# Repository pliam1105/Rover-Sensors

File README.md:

# Rover Sensors

## Overview
A prototype of a rover that can be used to collect data, in order to determine the habitability of a planet.

## Sensors
This rover contains the following sensors:
* Temperature-Humidity
* Gas
* Light
* Pressure and Altitude
* Air Quality
* UV
* GPS
* Geiger Radiation Counter

As well as an ESP-8266 Wi-Fi module for data transmission.<br>
These sensors and the Wi-Fi module are connected to an Arduino Mega (an Arduino Uno is also used between the Geiger Counter and the Arduino Mega). The Arduino in turn transmits the data, via some PHP files, to a database.

The sensors are connected to the Arduino using a custom-designed PCB, made using Fritzing:

<div style="overflow: hidden; width: 100%;">

</div>

## Database
The data of the sensors are stored on a MySQL database, currently on a shared hosting service.

The communication with the database is achieved via some [PHP files](RoverSensorsWeb/data_json.php), hosted on the website, which have access to database. 

## Website ([Link](http://pliamprojects.000webhostapp.com/rover))

The data can be accesed using the website, in the following way:

First, the user selects the mission, given a list of all available missions and their information.<br>
Then, on the home page, there is the following information:
* The average value for each type of data
* Information about the planet
* Its habitability based on the data collected
* Gauges that show the last value of each sensor
* The route of the rover in a map

For the website, I used VS Code and it was written in HTML, CSS, and JavaScript.<br>
([Source code](RoverSensorsWeb/data.php))

## Android Application ([Google Play](https://play.google.com/store/apps/details?id=com.pliamdev.pliam.roversensors))

I also made an Android application (using Android Studio) to access the sensors' data:

* First, the user selects a mission from a list retrieved from the database.
* The basic screen of the app is the page with the graphs.
* Another basic part of the app is the planet information page, where the user can view some information about the planet targeted by the mission (with links to the explanation of the data displayed), as well as the habitability of the planet based on the data retrieved by the rover.
* There is also a page where the user can view the rover’s location and route during the mission, retrieved from the database

([Source Code](RoverSensorsAndroid))
| | | | |
|:---:|:---:|:---:|:---:|
|  |  |  |  |

## Windows Application ([Microsoft Store](https://apps.microsoft.com/store/detail/rover-sensors/9PBLZ7BN15H7))
I created a UWP (Universal Windows Platform) Windows application, to view the data of the sensors, with Visual Studio. Its structure is the following (quite similar to the android application):
* The page where the user selects a mission to view the data for
* A page where the sensors’ data are displayed in graphs 
* The page where the user can view information about the planet as well as its habitability
* The page where the user can view the rover’s route

There is also the home page, where there is a dashboard containing all the above pages together.

([Source Code](RoverSensorsWindows))
| | |
|:---:|:---:|
|  |   |
|    |  |

<br>
<div style="margin-left: 20px"></div>

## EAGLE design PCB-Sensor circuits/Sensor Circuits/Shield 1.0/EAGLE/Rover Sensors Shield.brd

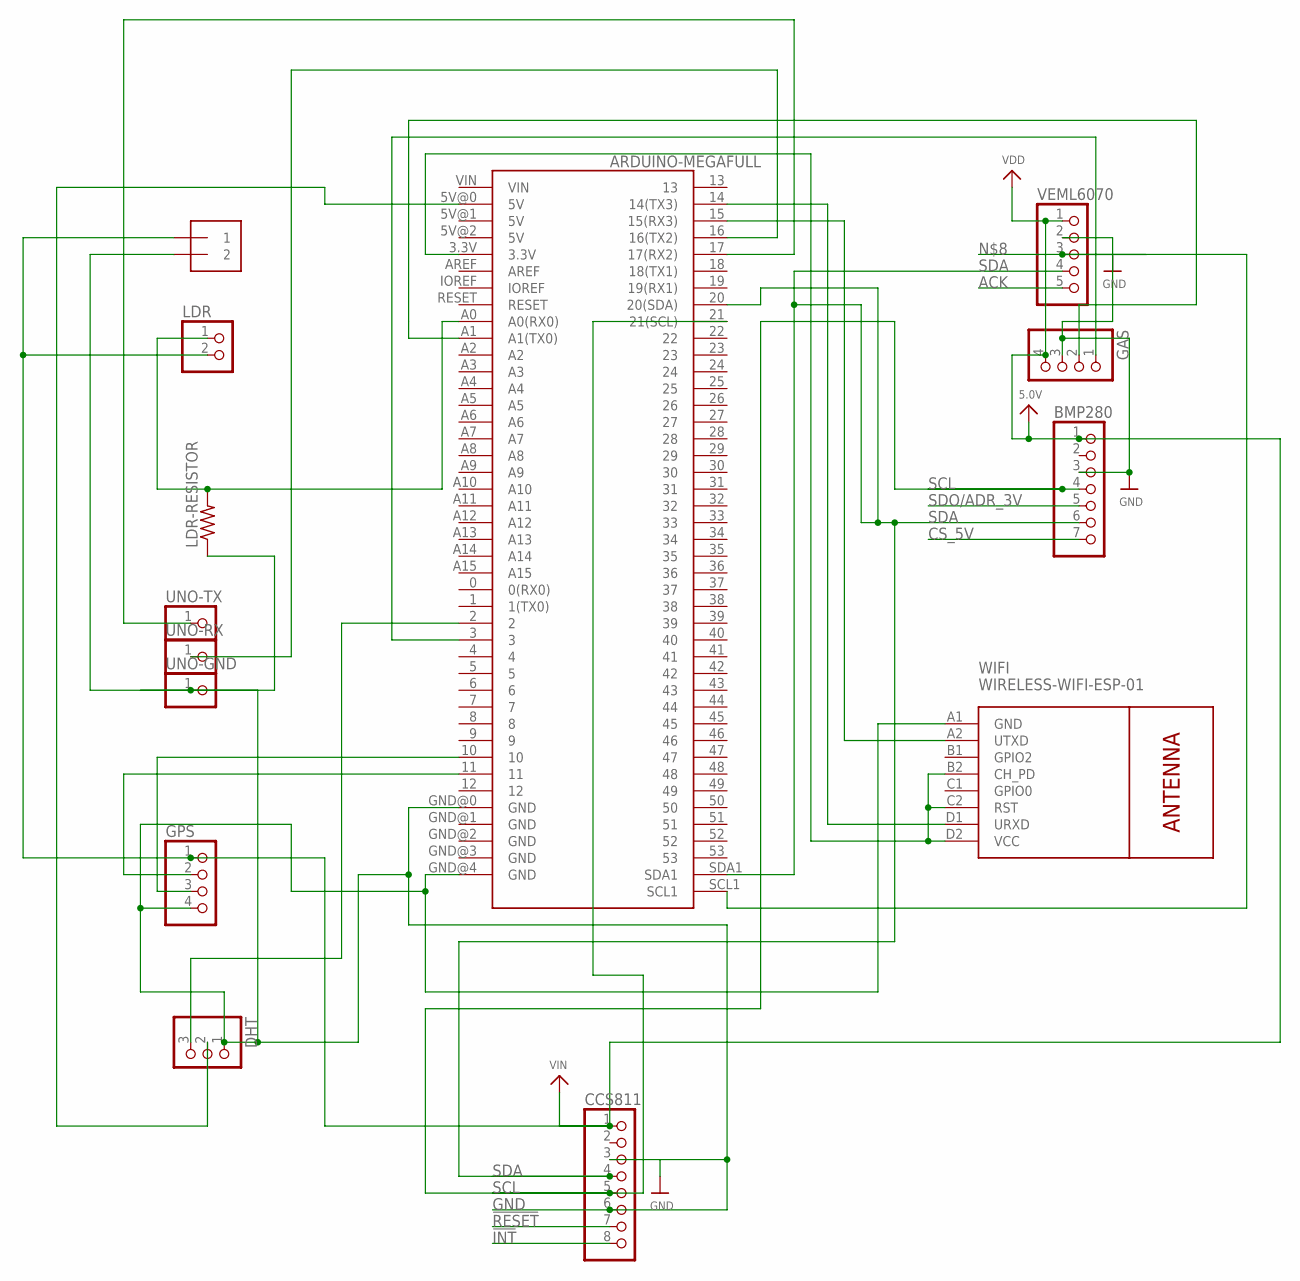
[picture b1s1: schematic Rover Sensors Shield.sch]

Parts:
BATTERY: 1X2-3.5MM
BMP280: HEADER-1X770MIL; 1X07_ROUND_70
CCS811: HEADER-1X870MIL; 1X08_ROUND_70
DHT: PINHD-1X3; 1X03
GAS: PINHD-1X4; 1X04
GPS: PINHD-1X4; 1X04
LDR: PINHD-1X2; 1X02
LDR-RESISTOR: R-US_0204/7; 0204/7
U2: ARDUINO-MEGAFULL; ARDUINO_MEGA
UNO-GND: PINHD-1X1; 1X01
UNO-RX: PINHD-1X1; 1X01
UNO-TX: PINHD-1X1; 1X01
VEML6070: HEADER-1X570MIL; 1X05_ROUND_70
WIFI: WIRELESS-WIFI-ESP-01

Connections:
!INT: CCS811.8
!RESET: CCS811.7
ACK: VEML6070.5
CS_5V: BMP280.7
GND: BATTERY.2, BMP280.3, CCS811.3, CCS811.6, DHT.1, GAS.3, GPS.4, LDR-RESISTOR.1, U2.GND@0 (GND), U2.GND@4 (GND), UNO-GND.1, VEML6070.2, WIFI.A1 (GND)
unnamed: GAS.2, U2.A1 (A1(TX0))
unnamed: GAS.1, U2.3
unnamed: U2.3.3V, WIFI.B2 (CH_PD), WIFI.C2 (RST), WIFI.D2 (VCC)
unnamed: U2.14 (14(TX3)), WIFI.D1 (URXD)
unnamed: U2.15 (15(RX3)), WIFI.A2 (UTXD)
unnamed: DHT.2, U2.5V@0 (5V)
unnamed: DHT.3, U2.2
unnamed: U2.SCL1, VEML6070.3
unnamed: GPS.3, U2.10
unnamed: GPS.2, U2.11
unnamed: U2.16 (16(TX2)), UNO-RX.1
unnamed: U2.17 (17(RX2)), UNO-TX.1
unnamed: LDR.1, LDR-RESISTOR.2, U2.A0 (A0(RX0))
SCL: BMP280.4, CCS811.5, U2.21 (21(SCL))
SDA: BMP280.6, CCS811.4, U2.20 (20(SDA)), U2.SDA1, VEML6070.4
SDO/ADR_3V: BMP280.5
VDD: BATTERY.1, BMP280.1, CCS811.1, GAS.4, GPS.1, LDR.2, VEML6070.1

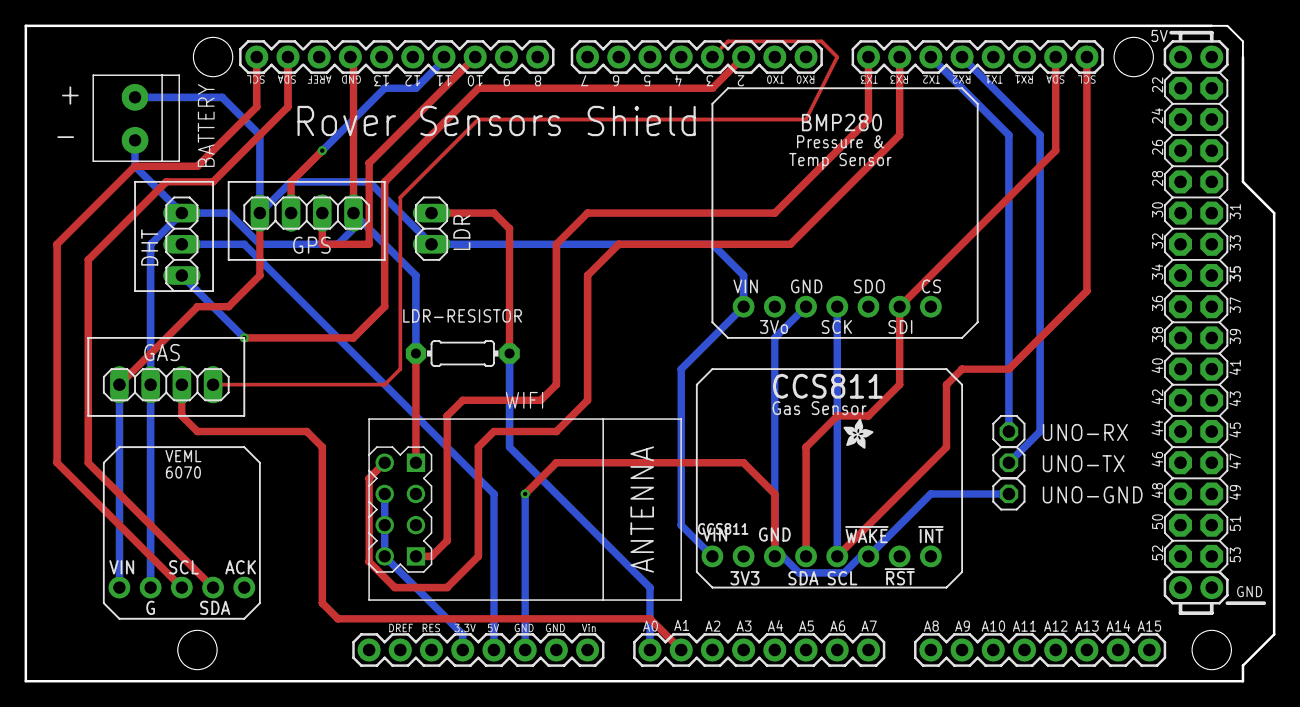
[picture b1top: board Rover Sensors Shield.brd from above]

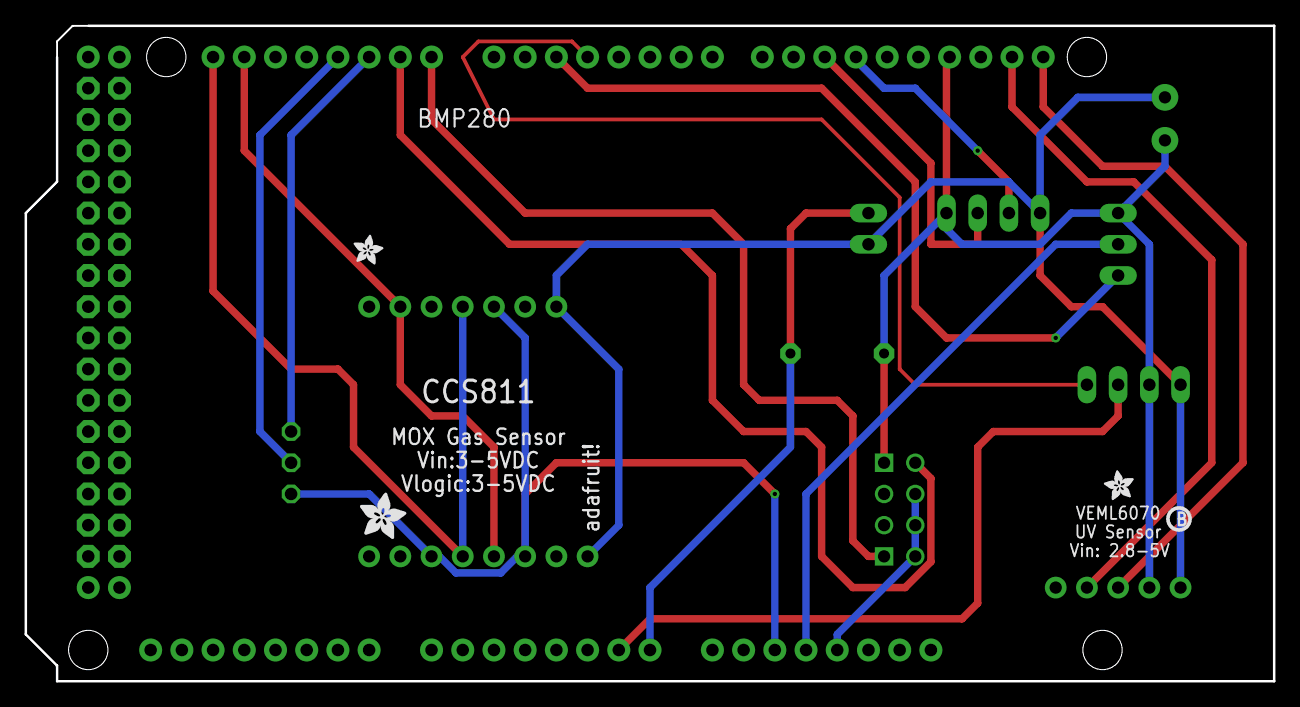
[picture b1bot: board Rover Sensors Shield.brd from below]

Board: 2 copper layers, 101.6 x 53.3 mm, 19 parts (4 on the bottom side), 17 nets.

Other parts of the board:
U$11, U$14, U$18: ADAFRUIT_2.5MM
U$15: PCBFEAT-REV-040
U$20: ADAFRUIT_3.5MM

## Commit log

2022-09-15 Upload Project Files
2022-09-16 Upload Rover Website
2022-09-16 Info Release
2022-09-26 Update files
2023-01-26 add description
2023-01-27 add pcb
2023-11-26 directory changes
2024-07-10 Update .gitignore files
2024-07-10 Update target API level
2024-07-10 Minor changes

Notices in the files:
parts and their libraries:
microbuilder: This work is placed in the public domain, and may be freely used for commercial and non-commercial work with the following conditions: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
diy-modules: Released under the Creative Commons Attribution 4.0 International License: http://creativecommons.org/licenses/by/4.0
